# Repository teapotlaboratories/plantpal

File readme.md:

# Teapotlabs Plantpal

Meet Teapotlabs Plantpal -  Your pal in plant care! This adorable device uses capacitive sensing to measure soil moisture. Its low-power e-paper display keeps you updated without draining energy. Plus, with the BME688 sensor, it is able to monitor air quality and CO2 levels, ensuring your plants thrive in optimal conditions.

Teapotlabs Plantpal is part of  [Teapotlabs open-hardware project](https://github.com/teapotlaboratories). 

## Sponsorship
Huge thanks to [PCBWay](https://www.pcbway.com) to sponsored this project! All PCB board and PCB Assembly in this project was using their rapid-prototyping services. The process from ordering to delivery of the device was really smooth and easy. We were really happy with the quality of the assembly and especially the customer support that was really easy to work with, where they help us identify and fix issue such as verifying BOM, checking components for assembly and even replacing damaged parts at no cost.

## Acknowledgement
The project won't be possible without the amazing work from people across the globe. The following are the reference to those awesome projects!

 - Soil moisture design from [b-parasite](https://github.com/rbaron/b-parasite) 
 - Solar energy Harvesting from [TSEM](https://hackaday.io/project/159139-tiny-solar-energy-module-tsem)
 - Antenna design from [Picoclick-C3](https://makermoekoe.gitbook.io/picoclick-c3)
 
## Specification

- [ESP32-C6FH4](https://www.espressif.com/sites/default/files/documentation/esp32-c6_datasheet_en.pdf): ESP32-C6 with 4 MB in-package flash
- [AEM10941](https://e-peas.com/product/aem10941): Solar energy harvesting
- USB-C for charging and programming
- ~20uA Deep-Sleep
- 1.54 Inch E-Paper Display
- Sensor:
	- `BME688` for Environmental Sensing
	- Built-in `Soil Moisture` sensor
	- `Battery voltage` sensing
- 500mA charge rate via USB
- 3.7 Volts LiPo Battery

## Revision
- **Revision 1**: Initial public release
- **Revision 2**: Remove via in pad
- **Revision 3**: 
	- Fix incorrect BOM component for D1
	- Fix D6 Polarity
	- Remove Power Gate
	- Change **Soil Sensor** `SENSE_OUT` pin
	- Add EPD power switch
	- Change to 4-layer board
	- Move BME688 to bottom layer
	- Improve antenna layout
- **Revision 4**: Re-wire EPD remaining power to +3V3D
- **Revision 5**: Re-trace Wifi antenna to conform with the new stack-up

## Release
- **Release 4.1**: Based on revision 4.0, with BoM changes.
  - Change charge rate resistor to 2K for 500mA
  - Update solar cell components to latest available  

## Schematics

Built using **KiCAD 7.0.5**
A detailed schematic can be found [here](https://raw.githubusercontent.com/teapotlaboratories/plantpal/main/hardware/schematic.pdf)

## Boards
 <p align="center">  <br><b>PCB Render</b></p>

Built using KiCAD, the board is design to be as small as possible with all components placed on the top side of the PCB.
> ⚠️ **The following design are based on revision 3 but is similar to revision 4.**

More images can be found [here](https://github.com/teapotlaboratories/plantpal/tree/main/docs/images)

| Top Board | Bottom Board |
|--|--|
|  |  |
|  |  |

 <p align="center"> <br><b>PCB Top and Bottom Layout</b></p> 

 <p align="center"> <br><b>Assembled Front Close-up</b></p> 
 
### Case and Showcase

Built using [TinkerCAD](https://www.tinkercad.com). The case are 3D printable with any generic 3D printer with/without support. The STL files are available [here](https://github.com/teapotlaboratories/plantpal/tree/main/hardware/case)
 <p align="center"><br><b>Case Open</b></p>

`BME688` sensor is available in the back, facing 3 small vents in the back of the case
 <p align="center"><br><b>BME688 Position</b></p>

#### Soil Moisture Sensing Showcase
Based on the amazing project in [b-parasite](https://github.com/rbaron/b-parasite), Plantpal has the built-in soil moisture sensor via capacitive sensing. Using capacitive sensing, enables the device to measure soil moisture without any traces exposed to the environment. See [rbaron's b-parasite](https://github.com/rbaron/b-parasite) project for more information on how the sensor works and more additional information to protect the soil moisture sensor!

<p align="center"><br><b>Soil Moisture Sensing Showcase</b></p>

## Measurement
Power consumption and solar charging current are measured using [Nordic PPK2](https://www.nordicsemi.com/Products/Development-hardware/Power-Profiler-Kit-2)  and [Joulescope](https://joulescope.com).
The following are the summary of the measurement:
- Deep-sleep : **22uA**
- Read Sensor, Update Display, and Store Data to Flash: **31mA @ 2.5s**
- Read Sensor, Update Display, Store Data to Flash, and Publish to MQTT: **54mA @ 3.77s**
- Direct Sunlight Solar Charge: **7.5mA**
  - Note: latest testing shows an average of 10mA
- Indirect Sunlight Solar Charge: **400uA**

> :warning: **Tested on Revision 4-equivalent board, but should be similar to Revision 4** 

<p align="center"><br><b>Deep-sleep</b></p>

<p align="center"><br><b>Read Sensor, Update Display, and Store Data to Flash</b></p>

<p align="center"><br><b>Read Sensor, Update Display, Store Data to Flash, and Publish to MQTT</b></p>

<p align="center"><br><b>Solar Charge - Direct Sunlight</b></p>

<p align="center"><br><b>Solar Charge - Indirect Sunlight</b></p>

More measurement can be found [here](https://github.com/teapotlaboratories/plantpal/tree/main/docs/measurement)

## Bill Of Materials
Most of the components are generic and can be bought from any electornics/semi-conductor distributor. The bill of materials can be downloaded [here](https://github.com/teapotlaboratories/plantpal/blob/main/hardware/bill_of_materials.csv).
The EPD display used and tested is `GDEY0154D67` from **GoodDisplay**. The following display should be compatible, but the example code would need to be adjusted:
- GDEW0154T8
- GDEW0154Z17
- GDEW0154Z04
- GDEW0154C39
- GDEW0154I9F

Those displays are available from AliExpress

## Programming
Programming the device can be done easily over the USB-C. 
Out of factory, the ESP32-C6 will be blank and need to be put in `bootloader` mode. The following is a step-by-step guide to initially program the device

  1. Plug-in the USB-C to host computer and check if the device is detected
  2. If not, check that you have the battery plug-in and try to shine the solar cell using any source of bright light ( phone flashlight, sun, lamp )
  3. Wait until the USB is detected in the host computer 
  4. Press and Hold `BOOT` and `RESET` button
  5. Release `RESET` button 
  6. Wait couple seconds
  7. Release `BOOT` button
  8. Plantpal should be in `bootloader` mode and you can flash it via `ESP-IDF` or `Arduino`

<p align="center"><br><b>Plantpal buttons</b></p>

A more detailed information about USB behavior on ESP32-C6 can be [here](https://docs.espressif.com/projects/esp-idf/en/latest/esp32c6/api-guides/usb-serial-jtag-console.html)

## How to Purchase
At the moment, we do not mass produce the device. The fastest way you can get the device is to order it directly from the manufacturer [here](https://link.teapotlabs.io/plantpal-order) (does **NOT** include the display and case).
You need to buy the display separately from Aliexpress or other distributor.

If you'd like to buy it from us fully assembled, we might be available and please contact contact@teapotlabs.io

## Disclaimer and notes
Some disclaimer about Plantpal:
- WiFi antenna is not tuned and not certified
- RTC components have not been tested
- The solar charge rate is 1.5mA lower than [Teapotlabs BWLR1E](https://github.com/teapotlaboratories/bwlr1e) even though they use the same components and configuration.
  - Note: latest testing shows an average of 10mA

## Questions?
For any questions feel free to create a issue or contact contact@teapotlabs.io

## License
The product is open-source! However, some part of library used under **firmware** or **hardware**, might have it's own license.
Please reach out or create a ticket if **Teapotlabs Plantpal** violated any licenses.

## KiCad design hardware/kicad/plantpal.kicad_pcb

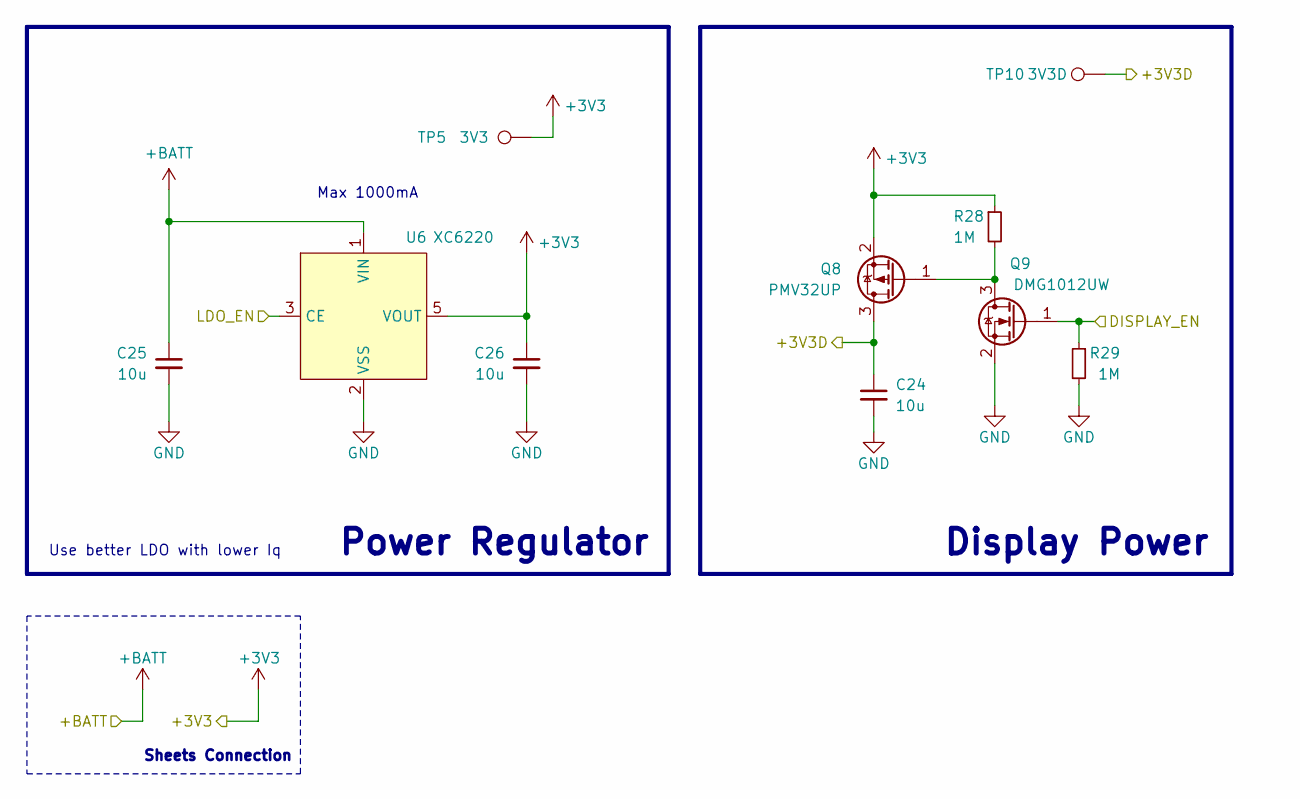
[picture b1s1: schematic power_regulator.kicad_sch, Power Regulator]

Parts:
C24, C25, C26: 10u; C_0603_1608Metric; Part Description Ceramic Capacitor 10V 10uF X5R ±10% 0603
Q8: PMV32UP; SOT-23; Part Description MOSFET P Channel 20V 4A 52mΩ@4.5V
Q9: DMG1012UW; SOT-323_SC-70; Part Description MOSFET N Channel 20V 1A 450mΩ@4.5V 600m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
R28, R29: 1M; R_0402_1005Metric; Part Description Resistor 62.5mW ±1% 1MΩ
TP5: 3V3; TestPoint_Pad_D1.0mm
TP10: 3V3D; TestPoint_Pad_D1.0mm
U6: XC6220; SOT-23-5; Part Description LDO Voltage Regulators 1A

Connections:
+3V3: C26.1, Q8.2 (S), R28.1, TP5.1, U6.5 (VOUT); also elsewhere on the board
+BATT: C25.1, U6.1 (VIN); also elsewhere on the board
/+3V3D: C24.1, Q8.3 (D), TP10.1; also elsewhere on the board
/Main Controller/DISPLAY_EN: Q9.1 (G), R29.1; also elsewhere on the board
/Power Regulator/LDO_EN: U6.3 (CE); also elsewhere on the board
GND: C24.2, C25.2, C26.2, Q9.2 (S), R29.2, U6.2 (VSS); also elsewhere on the board
unnamed: Q8.1 (G), Q9.3 (D), R28.2

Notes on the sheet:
Use better LDO with lower Iq
Max 1000mA
Display Power
Sheets Connection
Power Regulator

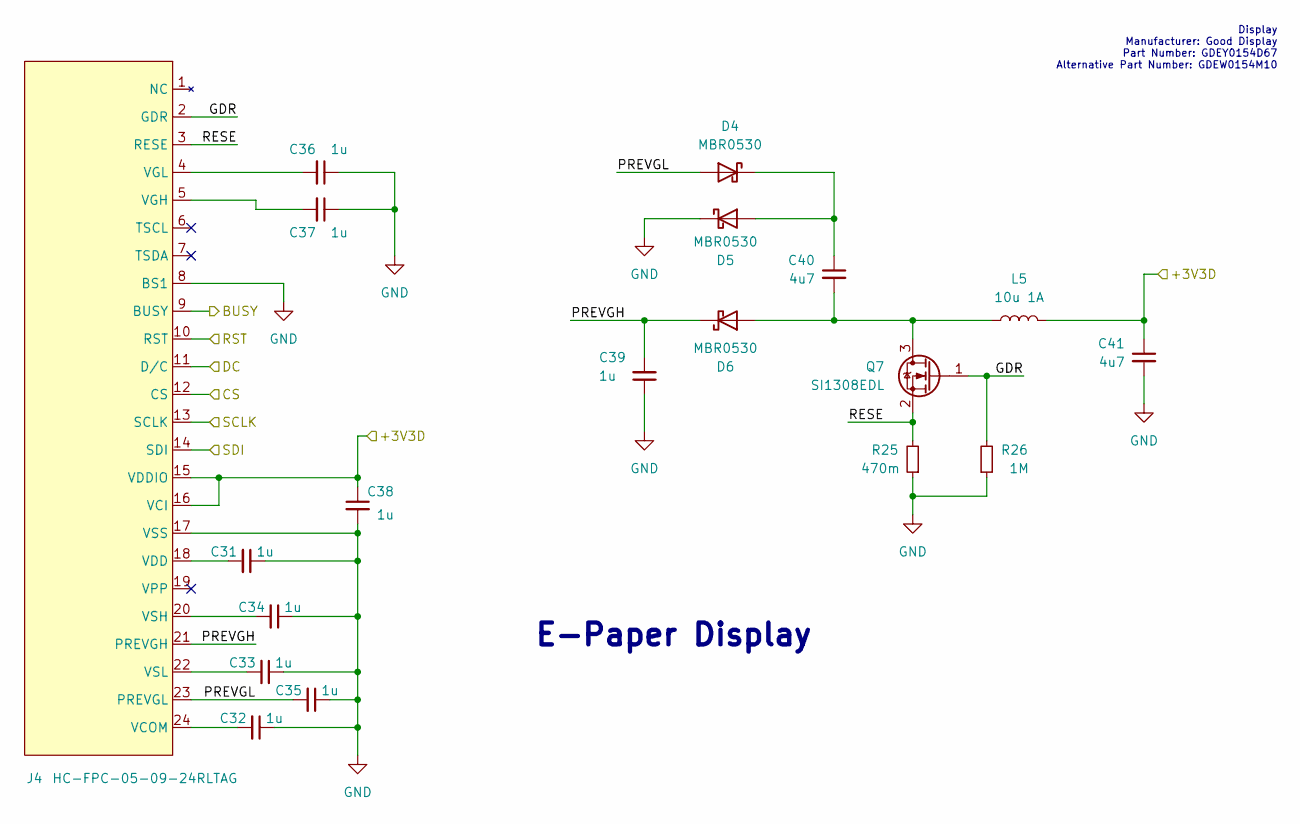
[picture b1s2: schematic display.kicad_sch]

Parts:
C31, C32, C33, C34, C35, C36, C37, C38, C39: 1u; C_0402_1005Metric; Part Description Ceramic Capacitors 50V 1uF X5R ±10%
C40, C41: 4u7; C_0603_1608Metric; Part Description Ceramic Capacitors 25V 4.7uF X5R ±10%
D4, D5, D6: MBR0530; D_SOD-123; Part Description Schottky Barrier Diodes 30V 430mV@500mA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
J4: HC-FPC-05-09-24RLTAG; FPC-SMD_24P-P0.50_HC-FPC-05-09-24RLTAG; Part Description FFC & FPC Connectors Clamshell 24P Bott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
L5: 10u 1A; L_Changjiang_FNR4012S; Part Description Power Inductors 1A 10uH ±20% 1.1A SMD,4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
Q7: SI1308EDL; SOT-323_SC-70; Part Description MOSFET N Channel 30V 1.4A 132mΩ@10V,1.4A
R25: 470m; R_0402_1005Metric; Part Description Resistor 125mW ±1% 470mΩ
R26: 1M; R_0402_1005Metric; Part Description Resistors 100mW ±1% 1MΩ

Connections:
/+3V3D: C38.1, C41.1, J4.15 (VDDIO), J4.16 (VCI), L5.1; also elsewhere on the board
/Display/BUSY: J4.9 (BUSY); also elsewhere on the board
/Display/CS: J4.12 (CS); also elsewhere on the board
/Display/DC: J4.11 (D/C); also elsewhere on the board
/Display/GDR: J4.2 (GDR), Q7.1 (G), R26.2
/Display/PREVGH: C39.2, D6.1 (K), J4.21 (PREVGH)
/Display/PREVGL: C35.2, D4.2 (A), J4.23 (PREVGL)
/Display/RESE: J4.3 (RESE), Q7.2 (S), R25.2
/Display/RST: J4.10 (RST); also elsewhere on the board
/Display/SCLK: J4.13 (SCLK); also elsewhere on the board
/Display/SDI: J4.14 (SDI); also elsewhere on the board
GND: C31.1, C32.1, C33.1, C34.1, C35.1, C36.1, C37.1, C38.2, C39.1, C41.2, D5.1 (K), J4.8 (BS1), J4.17 (VSS), R25.1, R26.1; also elsewhere on the board
unnamed: C40.1, D4.1 (K), D5.2 (A)
unnamed: C40.2, D6.2 (A), L5.2, Q7.3 (D)
unnamed: C32.2, J4.24 (VCOM)
unnamed: C31.2, J4.18 (VDD)
unnamed: C37.2, J4.5 (VGH)
unnamed: C36.2, J4.4 (VGL)
unnamed: C34.2, J4.20 (VSH)
unnamed: C33.2, J4.22 (VSL)

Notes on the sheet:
Display Manufacturer: Good Display Part Number: GDEY0154D67 Alternative Part Number: GDEW0154M10
E-Paper Display

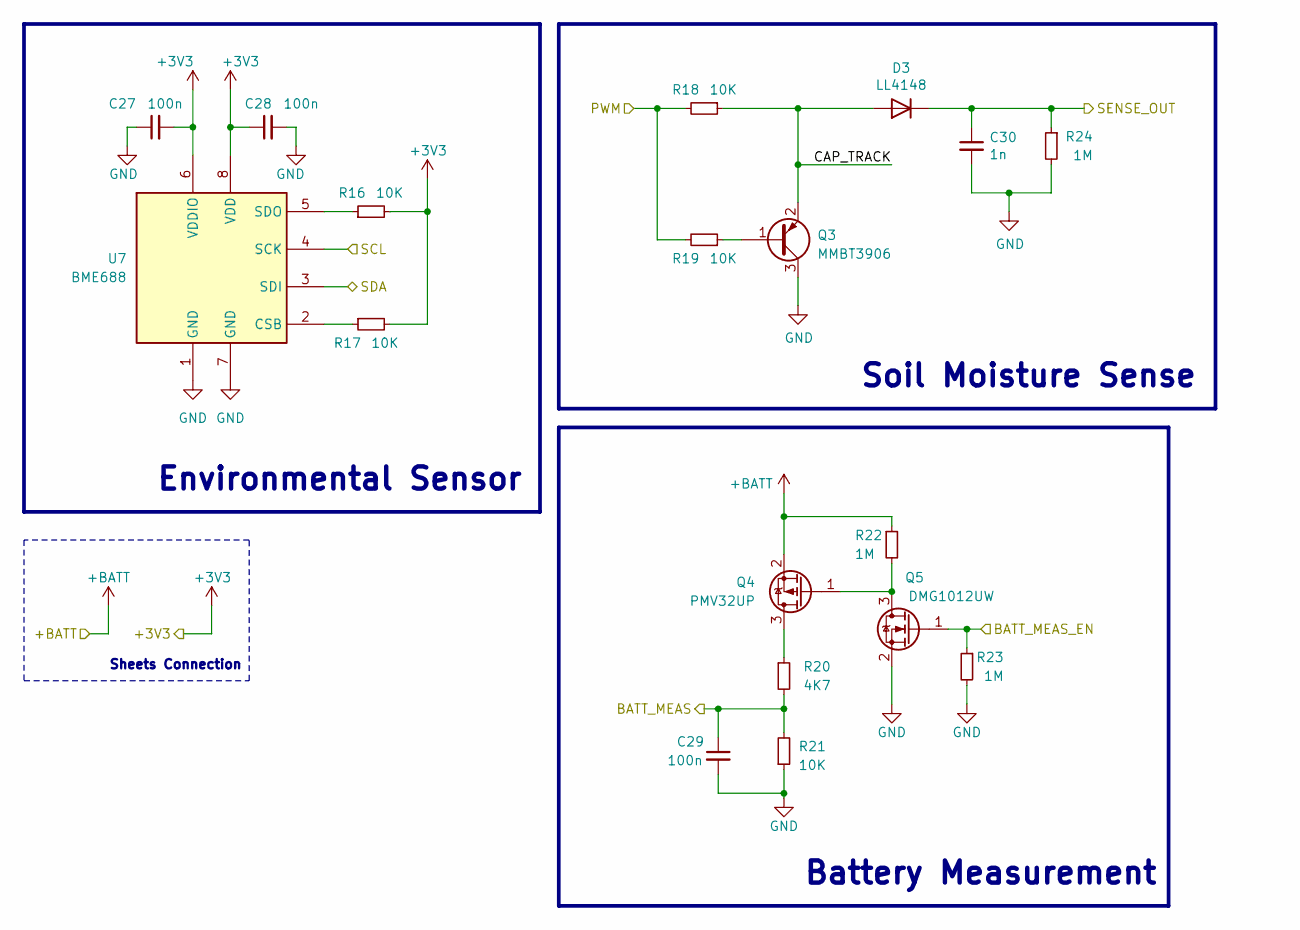
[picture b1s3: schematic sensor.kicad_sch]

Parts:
C27, C28, C29: 100n; C_0402_1005Metric; Part Description Ceramic Capacitor 16V 100nF X7R ±10%
C30: 1n; C_0402_1005Metric; Part Description Ceramic Capacitors 50V 1nF X7R ±10%
D3: LL4148; D_MiniMELF; Part Description Switching Diode 75V 500mW 1V@10mA 4ns 0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
Q3: MMBT3906; SOT-23; Part Description Bipolar Transistors 40V 200mW 100@10mA,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
Q4: PMV32UP; SOT-23; Part Description MOSFET P Channel 20V 4A 52mΩ@4.5V
Q5: DMG1012UW; SOT-323_SC-70; Part Description MOSFET N Channel 20V 1A 450mΩ@4.5V 600m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
R16, R17, R18, R19, R21: 10K; R_0402_1005Metric; Part Description Resistors 62.5mW ±1% 10kΩ
R20: 4K7; R_0402_1005Metric; Part Description Resistor 62.5mW ±1% 4.7kΩ
R22, R23, R24: 1M; R_0402_1005Metric; Part Description Resistor 62.5mW ±1% 1MΩ
U7: BME688; BME680-PSON80P300X300X100-8N; Part Description Gas, Humidity, Pressure, Temperature Se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

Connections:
+3V3: C27.2, C28.1, R16.2, R17.2, U7.6 (VDDIO), U7.8 (VDD); also elsewhere on the board
+BATT: Q4.2 (S), R22.1; also elsewhere on the board
/Main Controller/BATT_MEAS: C29.1, R20.2, R21.2; also elsewhere on the board
/Main Controller/BATT_MEAS_EN: Q5.1 (G), R23.1; also elsewhere on the board
/Main Controller/PWM: R18.2, R19.2; also elsewhere on the board
/Main Controller/SENSE_OUT: C30.1, D3.1 (K), R24.1; also elsewhere on the board
/SCL: U7.4 (SCK); also elsewhere on the board
/SDA: U7.3 (SDI); also elsewhere on the board
/Sensor/CAP_TRACK: D3.2 (A), Q3.2 (E), R18.1
GND: C27.1, C28.2, C29.2, C30.2, Q3.3 (C), Q5.2 (S), R21.1, R23.2, R24.2, U7.1 (GND), U7.7 (GND); also elsewhere on the board
unnamed: Q3.1 (B), R19.1
unnamed: Q4.3 (D), R20.1
unnamed: Q4.1 (G), Q5.3 (D), R22.2
unnamed: R17.1, U7.2 (CSB)
unnamed: R16.1, U7.5 (SDO)

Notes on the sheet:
Sheets Connection
Soil Moisture Sense
Battery Measurement
Environmental Sensor

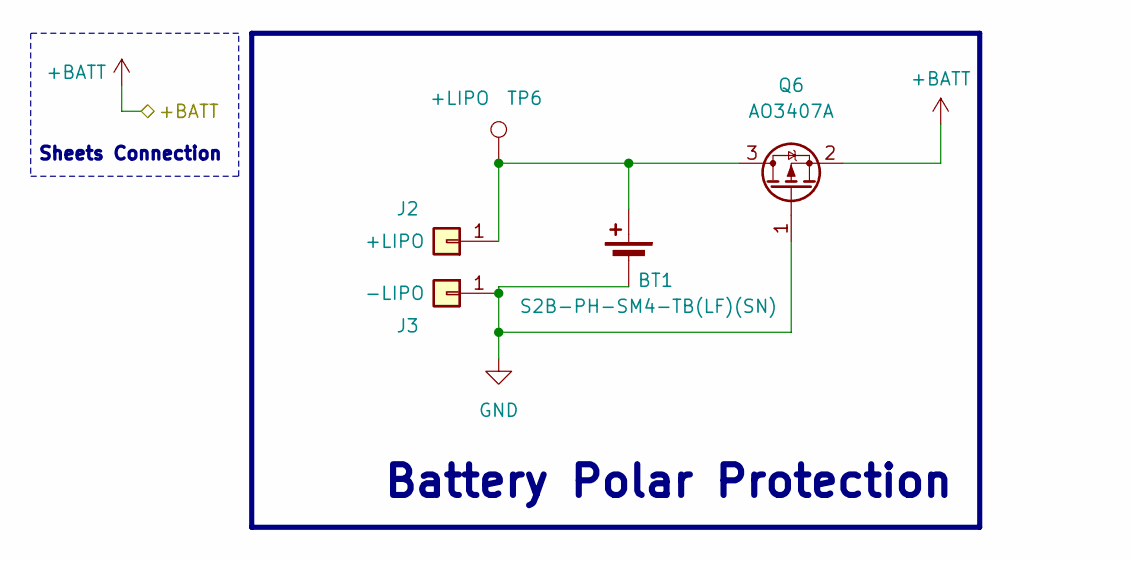
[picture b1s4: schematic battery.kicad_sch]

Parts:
BT1: S2B-PH-SM4-TB(LF)(SN); JST_PH_S2B-PH-SM4-TB_1x02-1MP_P2.00mm_Horizontal; Part Description Wire To Board Connector 1x2P PH 2mm Mal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
J2: +LIPO; TestPoint_THTPad_D1.0mm_Drill0.5mm; Part Description On-board Pad
J3: -LIPO; TestPoint_THTPad_D1.0mm_Drill0.5mm; Part Description On-board Pad
Q6: AO3407A; SOT-23; Part Description MOSFET P Channel 30V 4.3A 48mΩ@10V,4.3A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
TP6: +LIPO; TestPoint_Pad_D1.0mm

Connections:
+BATT: Q6.2 (S); also elsewhere on the board
GND: BT1.2 (-), J3.1, Q6.1 (G); also elsewhere on the board
unnamed: BT1.1 (+), J2.1, Q6.3 (D), TP6.1

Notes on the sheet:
Battery Polar Protection
Sheets Connection

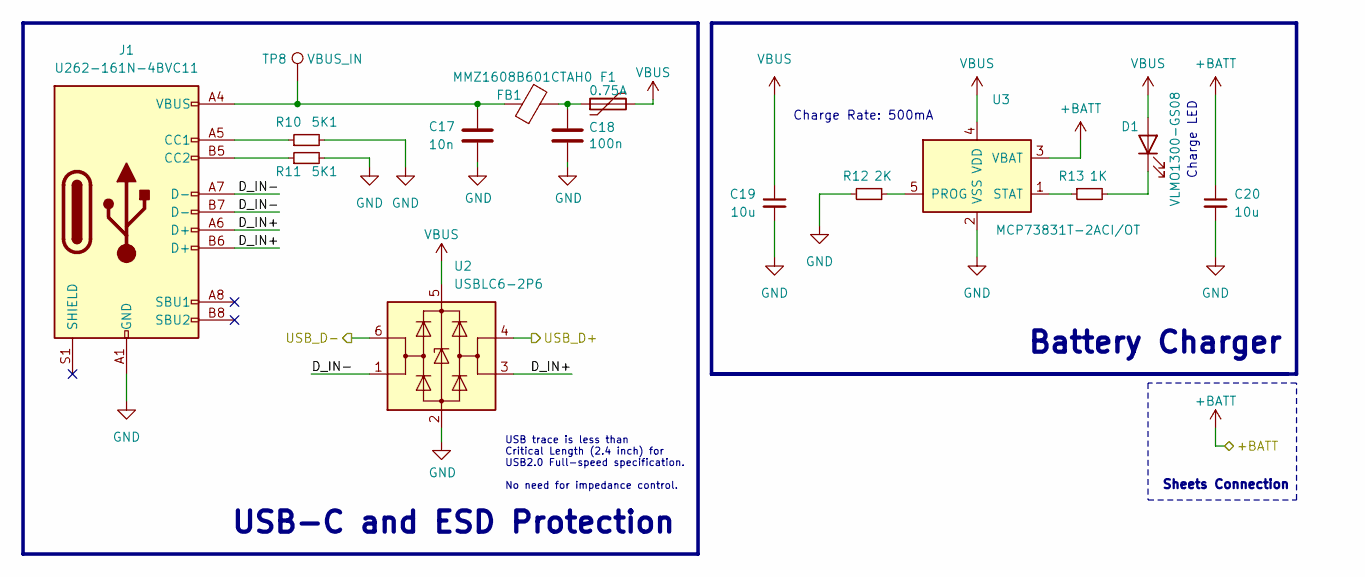
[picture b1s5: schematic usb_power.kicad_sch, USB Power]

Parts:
C17: 10n; C_0402_1005Metric; Part Description Ceramic Capacitors 16V 10nF X7R ±10%
C18: 100n; C_0402_1005Metric; Part Description Ceramic Capacitor 16V 100nF X7R ±10%
C19, C20: 10u; C_0603_1608Metric; Part Description Ceramic Capacitor 10V 10uF X5R ±10% 0603
D1: VLMO1300-GS08; LED_0603_1608Metric; Part Description Orange 2V 20mA
F1: 0.75A; Fuse_0805_2012Metric; Part Description Resettable Fuses 6V 750mA 40A 1.5A
FB1: MMZ1608B601CTAH0; L_0603_1608Metric; Part Description Ferrite Beads 400mΩ ±25% 600Ω@100MHz
J1: U262-161N-4BVC11; USB_C_Receptacle_XKB_U262-16XN-4BVC11; Part Description USB Connectors Type-C 3A USB 3.1 16P
R10, R11: 5K1; R_0402_1005Metric; Part Description Resistor 62.5mW ±1% 5.1kΩ
R12: 2K; R_0402_1005Metric; Part Description Resistor 62.5mW ±1% 2kΩ
R13: 1K; R_0402_1005Metric; Part Description Resistor 62.5mW ±1% 1kΩ
TP8: VBUS_IN; TestPoint_Pad_D1.0mm
U2: USBLC6-2P6; SOT-666; Part Description ESD Protection 6V 17V 2 Unidirectional 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
U3: MCP73831T-2ACI/OT; SOT-23-5; Part Description Battery Management IC 6V LiPoly 1500mA

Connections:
+BATT: C20.1, U3.3 (VBAT); also elsewhere on the board
/Main Controller/USB_D+: U2.4 (I/O2); also elsewhere on the board
/Main Controller/USB_D-: U2.6 (I/O1); also elsewhere on the board
/USB Power/D_IN+: J1.A6 (D+), J1.B6 (D+), U2.3 (I/O2)
/USB Power/D_IN-: J1.A7 (D-), J1.B7 (D-), U2.1 (I/O1)
GND: C17.2, C18.2, C19.2, C20.2, J1.A1 (GND), J1.A12 (GND), J1.B1 (GND), J1.B12 (GND), R10.2, R11.2, R12.2, U2.2 (GND), U3.2 (VSS); also elsewhere on the board
unnamed: C17.1, FB1.1, J1.A4 (VBUS), J1.A9 (VBUS), J1.B4 (VBUS), J1.B9 (VBUS), TP8.1
unnamed: C18.1, F1.1, FB1.2
unnamed: D1.1 (K), R13.2
unnamed: J1.A5 (CC1), R10.1
unnamed: J1.B5 (CC2), R11.1
unnamed: R12.1, U3.5 (PROG)
unnamed: R13.1, U3.1 (STAT)
VBUS: C19.1, D1.2 (A), F1.2, U2.5 (VBUS), U3.4 (VDD)

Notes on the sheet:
Sheets Connection
Charge Rate: 500mA
Battery Charger
USB-C and ESD Protection
Charge LED
USB trace is less than Critical Length (2.4 inch) for USB2.0 Full-speed specification. No need for impedance control.

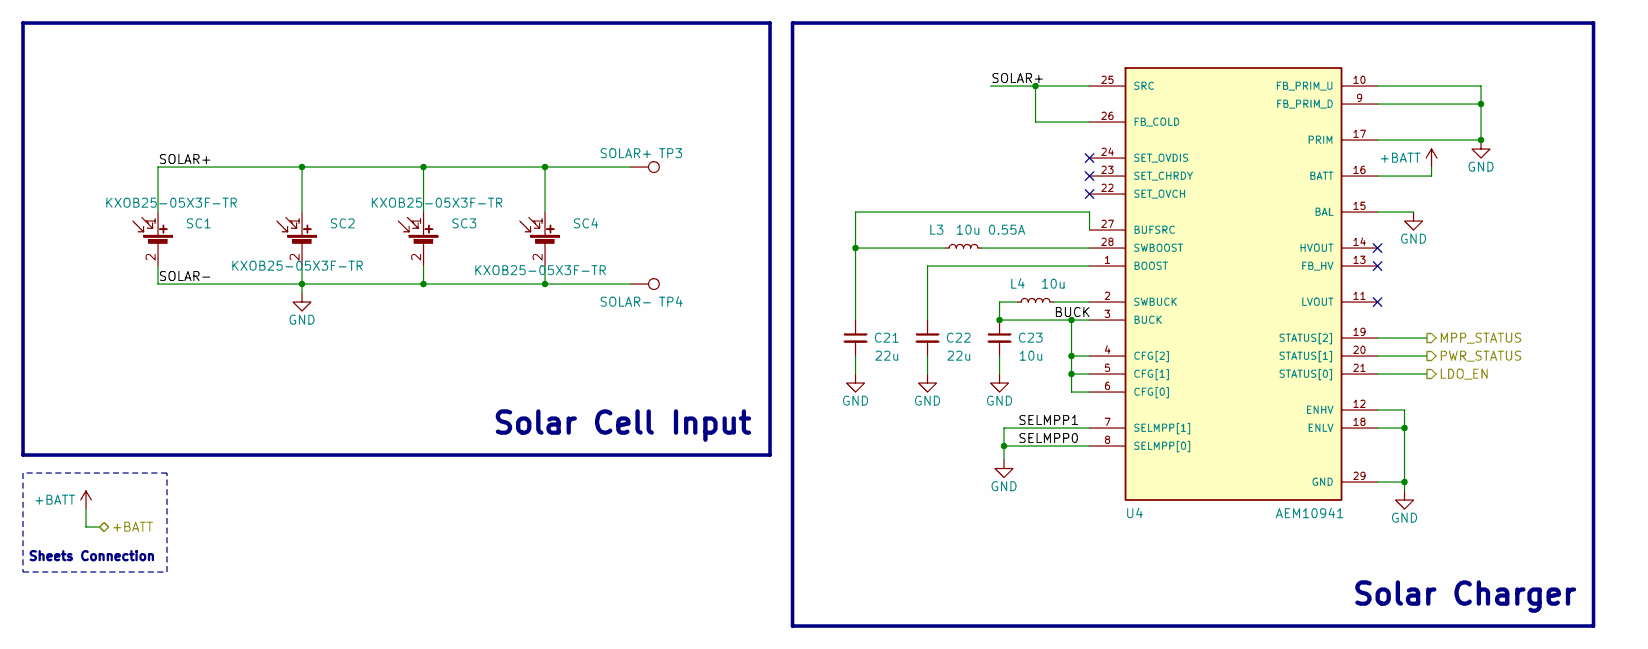
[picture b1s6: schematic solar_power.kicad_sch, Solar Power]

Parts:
C21, C22: 22u; C_0603_1608Metric; Part Description Ceramic Capacitors 10V 22uF X5R ±20%
C23: 10u; C_0603_1608Metric; Part Description Ceramic Capacitor 10V 10uF X5R ±10%
L3: 10u 0.55A; IND_LPS4012-103MRB; Part Description Power Inductors - SMD 10uH Shld 20% 1.1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
L4: 10u; L_0603_1608Metric; Part Description Power Inductors 10uH ±20% 90mA 1.05Ω
SC1, SC2, SC3, SC4: KXOB25-05X3F-TR; KXOB25-05X3F; Part Description Solar Cell G3 Thin 2.07V 30.7MW
TP3: SOLAR+; TestPoint_Pad_D1.0mm
TP4: SOLAR-; TestPoint_Pad_D1.0mm
U4: AEM10941; QFN-28-1EP_5x5mm_P0.5mm_EP3.35x3.35mm; Part Description PMIC IC - Photovoltaic Energy Harvestin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

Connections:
+BATT: U4.16 (BATT); also elsewhere on the board
/Main Controller/MPP_STATUS: U4.19 (STATUS[2]); also elsewhere on the board
/Main Controller/PWR_STATUS: U4.20 (STATUS[1]); also elsewhere on the board
/Power Regulator/LDO_EN: U4.21 (STATUS[0]); also elsewhere on the board
/Solar Power/BUCK: C23.1, L4.1, U4.3 (BUCK), U4.4 (CFG[2]), U4.5 (CFG[1]), U4.6 (CFG[0])
/Solar Power/SOLAR+: SC1.1 (+), SC2.1 (+), SC3.1 (+), SC4.1 (+), TP3.1, U4.25 (SRC), U4.26 (FB_COLD)
GND: C21.2, C22.2, C23.2, SC1.2 (-), SC2.2 (-), SC3.2 (-), SC4.2 (-), TP4.1, U4.7 (SELMPP[1]), U4.8 (SELMPP[0]), U4.9 (FB_PRIM_D), U4.10 (FB_PRIM_U), U4.12 (ENHV), U4.15 (BAL), U4.17 (PRIM), U4.18 (ENLV), U4.29 (GND); also elsewhere on the board
unnamed: C22.1, U4.1 (BOOST)
unnamed: C21.1, L3.1, U4.27 (BUFSRC)
unnamed: L3.2, U4.28 (SWBOOST)
unnamed: L4.2, U4.2 (SWBUCK)

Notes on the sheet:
Solar Cell Input
Sheets Connection
Solar Charger

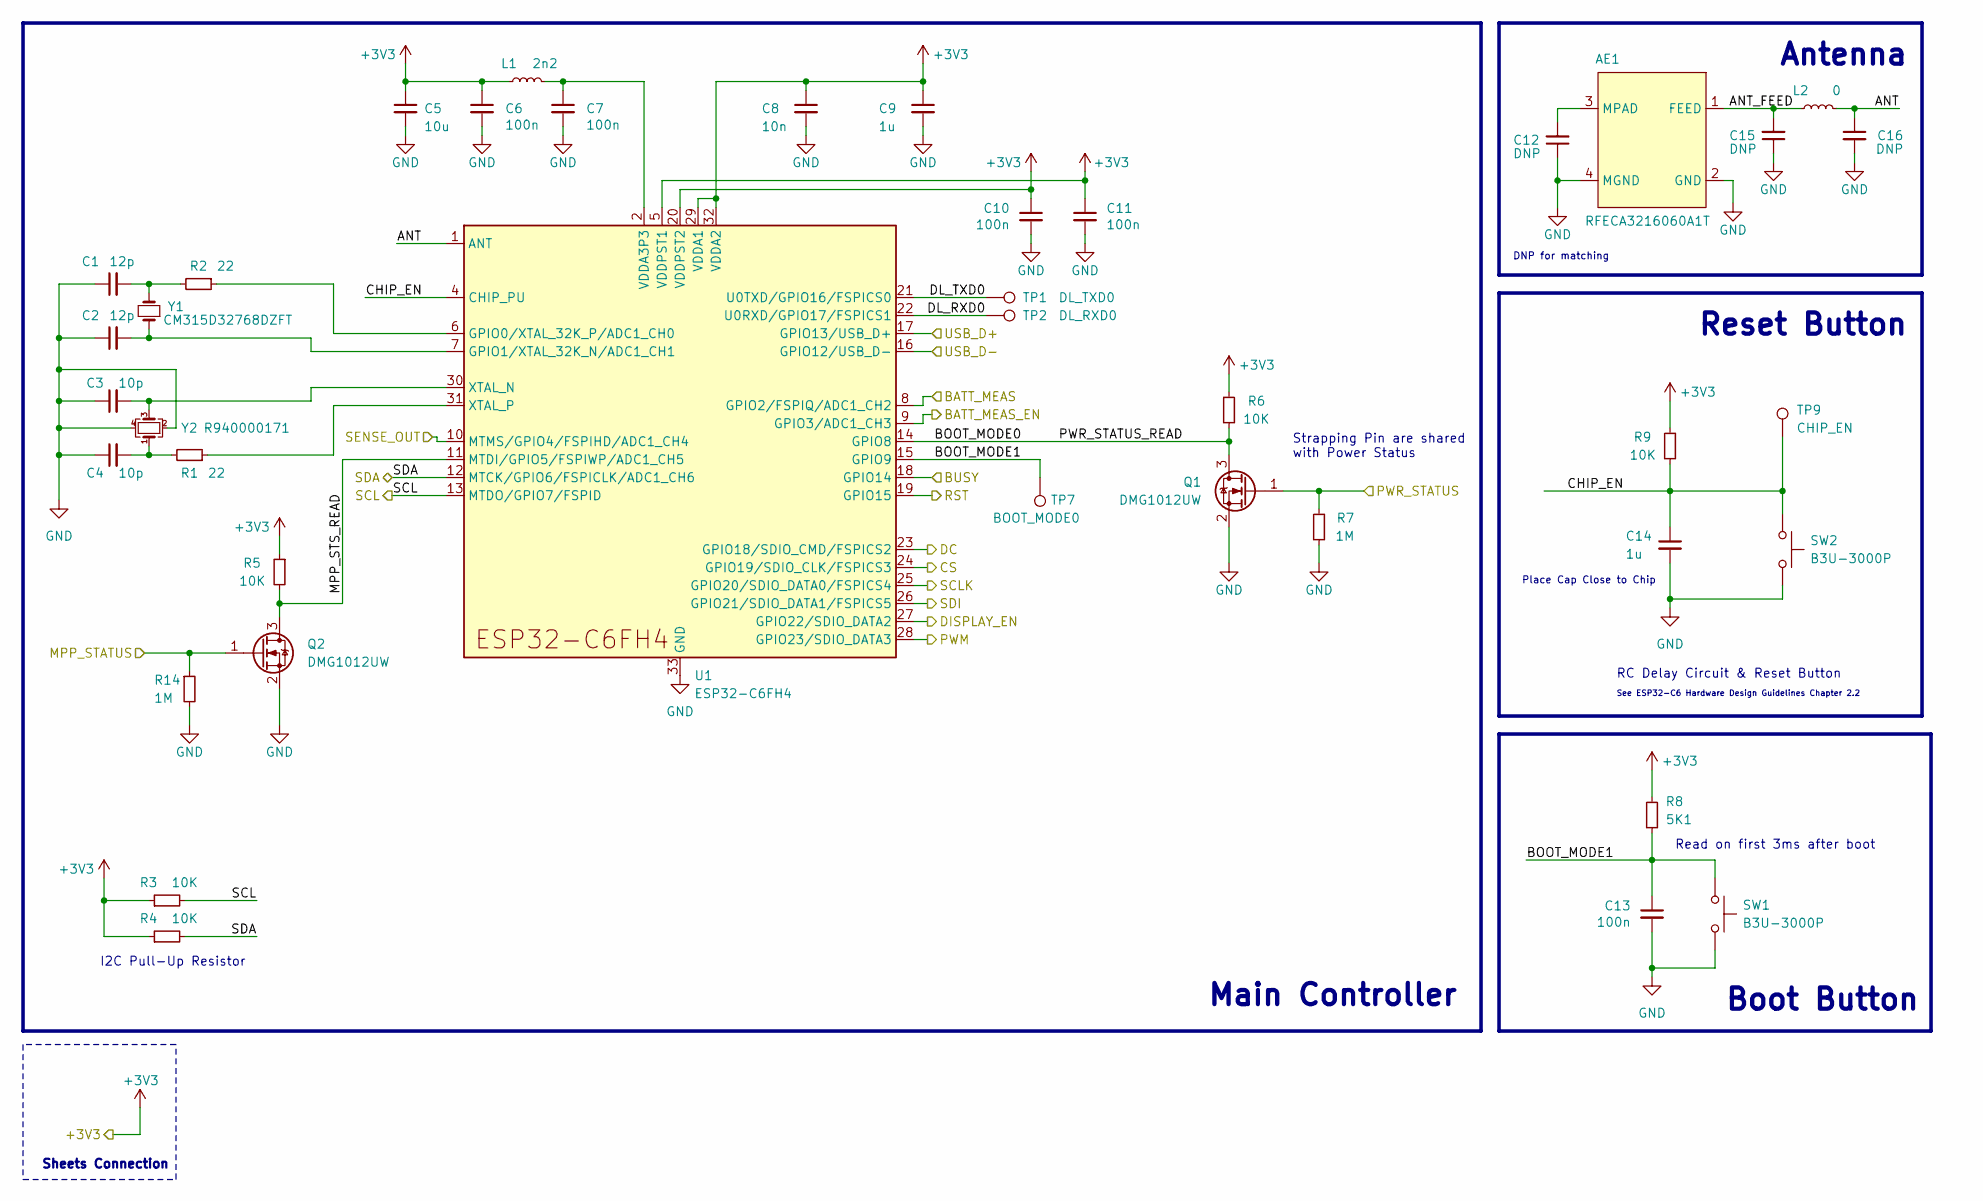
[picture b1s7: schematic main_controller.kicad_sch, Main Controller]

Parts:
AE1: RFECA3216060A1T; Part Description Chip RF Antenna 2.4GHz 2dBi
C1, C2: 12p; C_0402_1005Metric; Part Description Ceramic Capacitors 50V 12pF C0G ±1%
C3, C4: 10p; C_0402_1005Metric; Part Description Ceramic Capacitors 50V 10pF C0G ±1%
C5: 10u; C_0603_1608Metric; Part Description Ceramic Capacitor 10V 10uF X5R ±10% 0603
C6, C7, C10, C11, C13: 100n; C_0402_1005Metric; Part Description Ceramic Capacitor 16V 100nF X7R ±10%
C8: 10n; C_0402_1005Metric; Part Description Ceramic Capacitors 16V 10nF X7R ±10%
C9, C14: 1u; C_0402_1005Metric; Part Description Ceramic Capacitors 10V 1uF X7R ±10%
C12, C15, C16: DNP; C_0402_1005Metric
L1: 2n2; L_0402_1005Metric; Part Description Power Inductors 2.53A 2.2nH ±2%
L2: 0; L_0402_1005Metric; Part Description Resistor 62.5mW ±1% 0Ω
Q1, Q2: DMG1012UW; SOT-323_SC-70; Part Description MOSFET N Channel 20V 1A 450mΩ@4.5V,600m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
R1, R2: 22; R_0402_1005Metric; Part Description Resistor 62.5mW ±1% 22Ω
R3, R4, R5, R6, R9: 10K; R_0402_1005Metric; Part Description Resistors 62.5mW ±1% 10kΩ
R7, R14: 1M; R_0402_1005Metric; Part Description Resistor 62.5mW ±1% 1MΩ
R8: 5K1; R_0402_1005Metric; Part Description Resistor 62.5mW ±1% 5.1kΩ
SW1, SW2: B3U-3000P; SW_SPST_B3U-3000P; Part Description Tactile Switches NO 50mA 100MΩ 12V 1.59N
TP1: DL_TXD0; TestPoint_Pad_D1.0mm
TP2: DL_RXD0; TestPoint_Pad_D1.0mm
TP7: BOOT_MODE0; TestPoint_Pad_D1.0mm
TP9: CHIP_EN; TestPoint_Pad_D1.0mm
U1: ESP32-C6FH4; QFN-32-1EP_5x5mm_P0.5mm_EP3.6x3.6mm; Part Description Wireless SOC Bluetooth, WiFi Bluetooth 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
Y1: CM315D32768DZFT; Crystal_SMD_3215-2Pin_3.2x1.5mm; Part Description Crystals 32.768kHz 12.5pF ±20ppm
Y2: R940000171; Crystal_SMD_2016-4Pin_2.0x1.6mm; Part Description Crystals 40MHz 9pF ±10ppm

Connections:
+3V3: C5.1, C6.1, C8.1, C9.1, C10.1, C11.1, L1.1, R3.1, R4.1, R5.1, R6.1, R8.2, R9.1, U1.5 (VDDPST1), U1.20 (VDDPST2), U1.29 (VDDA1), U1.32 (VDDA2); also elsewhere on the board
/Display/BUSY: U1.18 (GPIO14); also elsewhere on the board
/Display/CS: U1.24 (GPIO19/SDIO_CLK/FSPICS3); also elsewhere on the board
/Display/DC: U1.23 (GPIO18/SDIO_CMD/FSPICS2); also elsewhere on the board
/Display/RST: U1.19 (GPIO15); also elsewhere on the board
/Display/SCLK: U1.25 (GPIO20/SDIO_DATA0/FSPICS4); also elsewhere on the board
/Display/SDI: U1.26 (GPIO21/SDIO_DATA1/FSPICS5); also elsewhere on the board
/Main Controller/ANT: C16.1, L2.2, U1.1 (ANT)
/Main Controller/ANT_FEED: AE1.1 (FEED), C15.2, L2.1
/Main Controller/BATT_MEAS: U1.8 (GPIO2/FSPIQ/ADC1_CH2); also elsewhere on the board
/Main Controller/BATT_MEAS_EN: U1.9 (GPIO3/ADC1_CH3); also elsewhere on the board
/Main Controller/BOOT_MODE0: Q1.3 (D), R6.2, U1.14 (GPIO8)
/Main Controller/BOOT_MODE1: C13.1, R8.1, SW1.1, TP7.1, U1.15 (GPIO9)
/Main Controller/CHIP_EN: C14.1, R9.2, SW2.1, TP9.1, U1.4 (CHIP_PU)
/Main Controller/DISPLAY_EN: U1.27 (GPIO22/SDIO_DATA2); also elsewhere on the board
/Main Controller/DL_RXD0: TP2.1, U1.22 (U0RXD/GPIO17/FSPICS1)
/Main Controller/DL_TXD0: TP1.1, U1.21 (U0TXD/GPIO16/FSPICS0)
/Main Controller/MPP_STATUS: Q2.1 (G), R14.1; also elsewhere on the board
/Main Controller/MPP_STS_READ: Q2.3 (D), R5.2, U1.11 (MTDI/GPIO5/FSPIWP/ADC1_CH5)
/Main Controller/PWM: U1.28 (GPIO23/SDIO_DATA3); also elsewhere on the board
/Main Controller/PWR_STATUS: Q1.1 (G), R7.1; also elsewhere on the board
/Main Controller/SENSE_OUT: U1.10 (MTMS/GPIO4/FSPIHD/ADC1_CH4); also elsewhere on the board
/Main Controller/USB_D+: U1.17 (GPIO13/USB_D+); also elsewhere on the board
/Main Controller/USB_D-: U1.16 (GPIO12/USB_D-); also elsewhere on the board
/SCL: R3.2, U1.13 (MTDO/GPIO7/FSPID); also elsewhere on the board
/SDA: R4.2, U1.12 (MTCK/GPIO6/FSPICLK/ADC1_CH6); also elsewhere on the board
GND: AE1.2 (GND), AE1.4 (MGND), C1.1, C2.1, C3.1, C4.1, C5.2, C6.2, C7.2, C8.2, C9.2, C10.2, C11.2, C12.1, C13.2, C14.2, C15.1, C16.2, Q1.2 (S), Q2.2 (S), R7.2, R14.2, SW1.2, SW2.2, U1.33 (GND), Y2.2, Y2.4; also elsewhere on the board
unnamed: AE1.3 (MPAD), C12.2
unnamed: C1.2, R2.2, Y1.2
unnamed: C4.2, R1.2, Y2.1
unnamed: C7.1, L1.2, U1.2 (VDDA3P3), U1.3 (VDDA3P3)
unnamed: R2.1, U1.6 (GPIO0/XTAL_32K_P/ADC1_CH0)
unnamed: C2.2, U1.7 (GPIO1/XTAL_32K_N/ADC1_CH1), Y1.1
unnamed: C3.2, U1.30 (XTAL_N), Y2.3
unnamed: R1.1, U1.31 (XTAL_P)

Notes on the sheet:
Place Cap Close to Chip
Reset Button
Antenna
DNP for matching
Main Controller
Sheets Connection
Boot Button
See ESP32-C6 Hardware Design Guidelines Chapter 2.2
RC Delay Circuit & Reset Button
Read on first 3ms after boot
I2C Pull-Up Resistor
Strapping Pin are shared with Power Status

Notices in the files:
readme.md:
License:
License: MIT
